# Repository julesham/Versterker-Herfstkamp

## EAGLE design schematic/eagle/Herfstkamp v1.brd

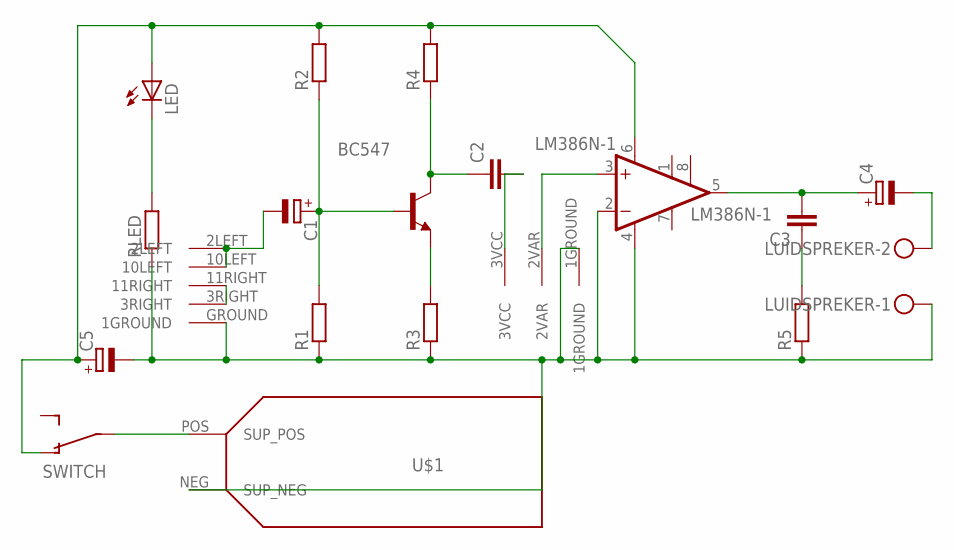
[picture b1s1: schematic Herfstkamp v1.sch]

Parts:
BC547: -NPN-TO92-CBE; TO92-CBE
C1: CPOL-EUE2-5; E2-5
C2, C3: C-EU050-024X044; C050-024X044
C4: CPOL-EUE2.5-6; E2,5-6
C5: CPOL-EUE3.5-8; E3,5-8
LED: LED5MM
LM386N-1: LM386N-1; DIL08
LUIDSPREKER: MKDSN1,5/2-5,08
POTENTIOMETER: POTENTIOMETERALPS
R1, R2, R3, R4, R5: R-EU_0207_10; 0207/10
RLED: R-EU_0207_10; 0207/10
SWITCH: OS102011MA1Q
U$1: BATTERY_HOLDER9V; BAT_HOLDER_9V
U$2: INPUTJACK; JACKSOCKET35RAPC4BHN2

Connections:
GROUND: C5.-, LM386N-1.2 (-IN), LM386N-1.4 (GND), LUIDSPREKER.1, POTENTIOMETER.1GROUND, R1.1, R3.1, R5.1, RLED.1, U$1.NEG (SUP_NEG), U$2.GROUND (1GROUND)
unnamed: LED.K (C), RLED.2
unnamed: BC547.E, R3.2
unnamed: BC547.C, C2.1, R4.1
unnamed: C2.2, POTENTIOMETER.3VCC
unnamed: C3.2, C4.+, LM386N-1.5 (OUT)
unnamed: C3.1, R5.2
unnamed: SWITCH.P$2, U$1.POS (SUP_POS)
unnamed: LM386N-1.3 (+IN), POTENTIOMETER.2VAR
unnamed: BC547.B, C1.+, R1.2, R2.1
unnamed: C5.+, LED.A, LM386N-1.6 (VS), R2.2, R4.2, SWITCH.P$1 (O1)
unnamed: C4.-, LUIDSPREKER.2
unnamed: U$2.3RIGHT, U$2.11RIGHT
unnamed: C1.-, U$2.2LEFT, U$2.10LEFT

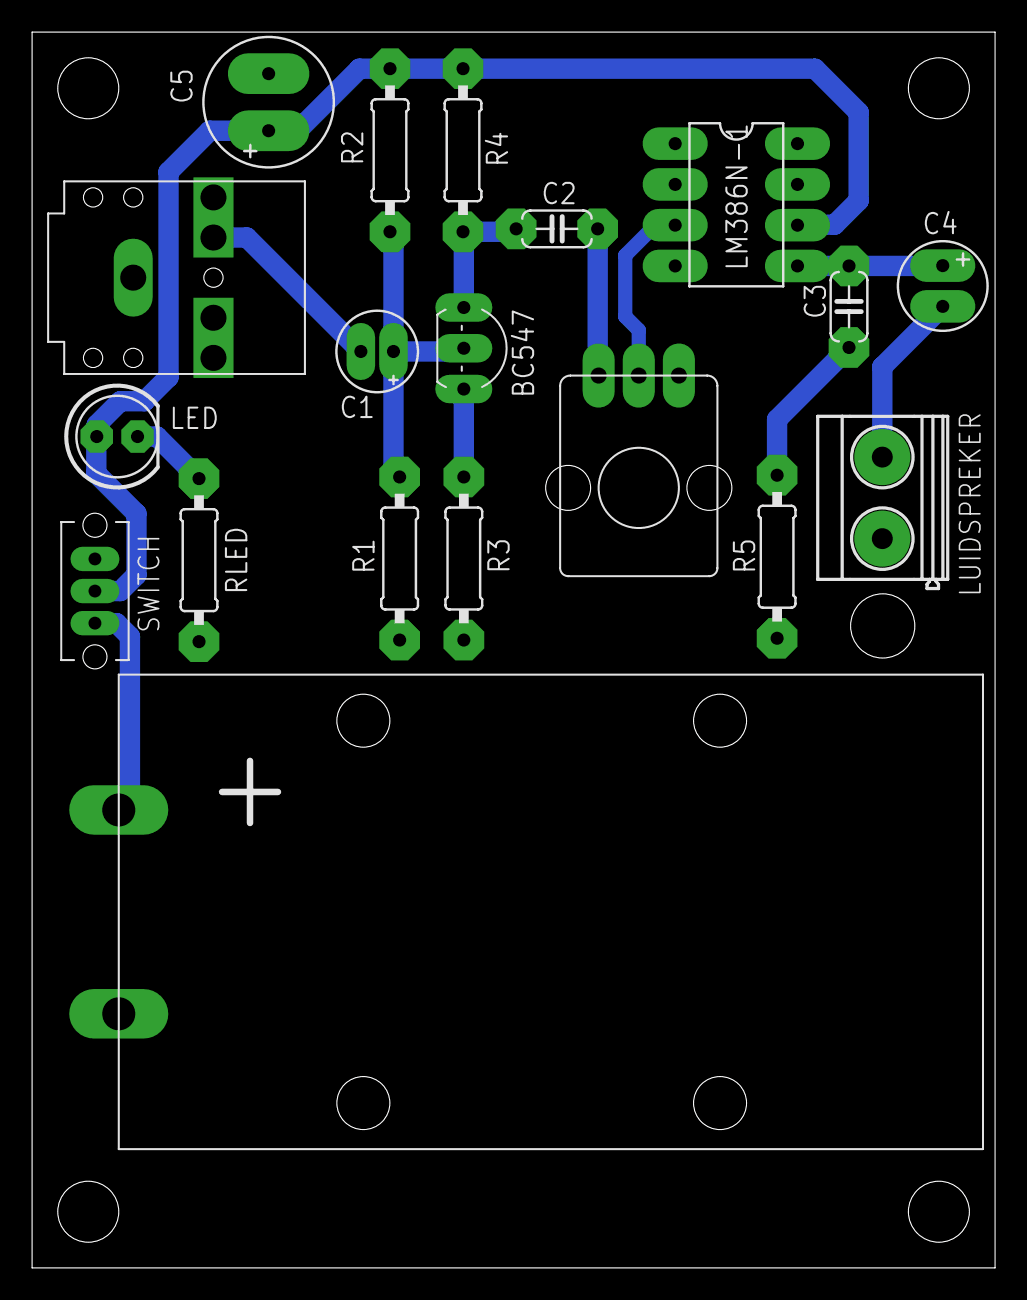
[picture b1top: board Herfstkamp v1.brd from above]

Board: 1 copper layer, 60.0 x 77.0 mm, 19 parts (0 on the bottom side), 14 nets.

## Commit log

2015-08-11 Versterker Herfstkamp
    x Datasheets
    x Eerste versie document
    x Schematics
2015-08-11 Alternatieve Structuur
    Niet eerst theorie en dan oefeningen, maar gemengd!
2015-08-11 V-Bron, Oefening 1, Kirchoff,
2015-08-12 Safe
2015-08-13 Begin EVUBOX
2015-08-13 Volumeknop +Diode
    x schrijven tekst
    x 3 testpersonen ?
    x lange tekst beter, verkorten alstmoet
2015-08-14 Begin Transistor
2015-08-18 Vervolg Transistor
2015-08-18 Voor het verkorten
2015-08-18 Shortened, behalve micro
2015-08-19 Passed the Gerd-Check
2015-08-19 Begin IC
2015-08-20 Daily Save
2015-08-21 Before Changes
2015-08-21 Gitignore
2015-08-25 25 August
2015-08-26 Marky Mark
2015-08-27 Invulblad en oplossingen
2015-09-01 Save voor aanpassing feedback
2015-09-02 Verbeteringen
2015-09-03 Last Update - Name Change
